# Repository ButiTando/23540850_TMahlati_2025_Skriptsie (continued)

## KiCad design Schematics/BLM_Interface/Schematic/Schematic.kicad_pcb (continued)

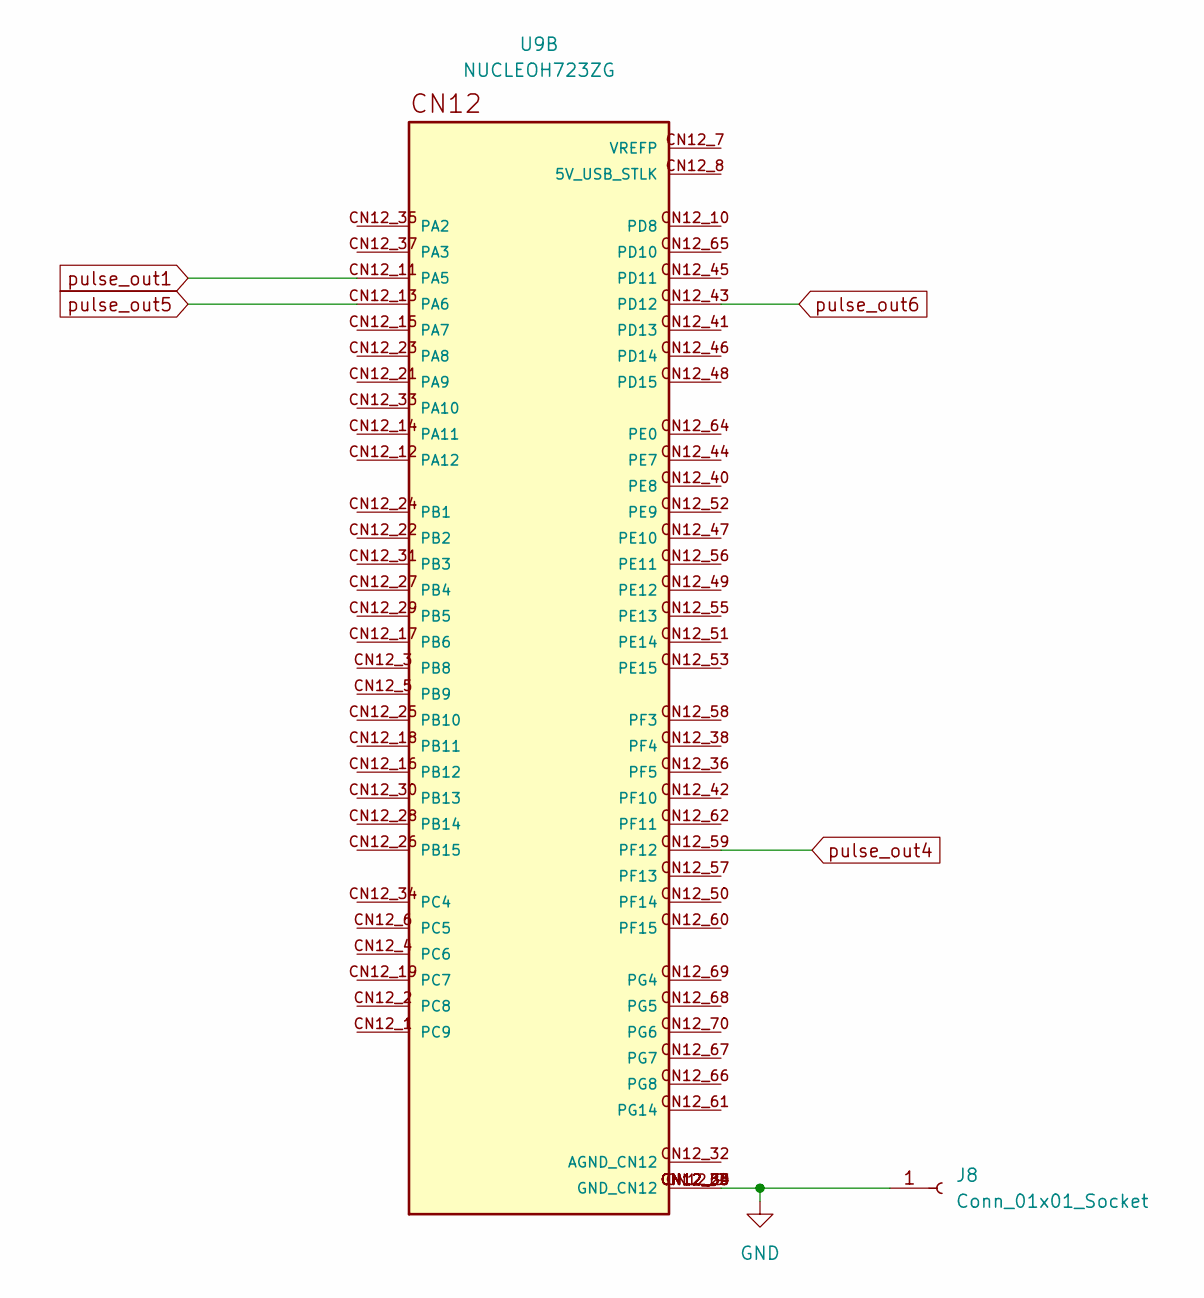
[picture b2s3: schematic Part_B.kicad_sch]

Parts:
J8: Conn_01x01_Socket; PinSocket_1x01_P2.54mm_Vertical
U9: NUCLEOH723ZG; MODULE_NUCLEOH723ZG; PARTREV 2

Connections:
GND: J8.1, U9.CN12_9 (GND_CN12), U9.CN12_20 (GND_CN12), U9.CN12_39 (GND_CN12), U9.CN12_54 (GND_CN12), U9.CN12_63 (GND_CN12); also elsewhere on the board
pulse_out1: U9.CN12_11 (PA5); also elsewhere on the board
pulse_out4: U9.CN12_59 (PF12); also elsewhere on the board
pulse_out5: U9.CN12_13 (PA6); also elsewhere on the board
pulse_out6: U9.CN12_43 (PD12); also elsewhere on the board

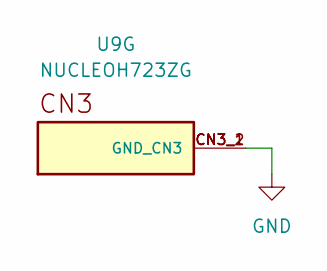
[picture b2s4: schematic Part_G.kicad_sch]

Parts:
U9: NUCLEOH723ZG; MODULE_NUCLEOH723ZG; PARTREV 2

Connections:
GND: U9.CN3_1 (GND_CN3), U9.CN3_2 (GND_CN3); also elsewhere on the board

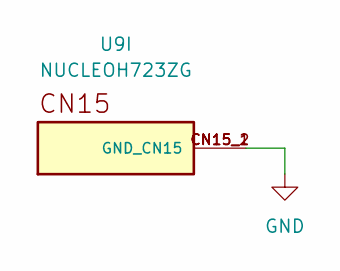
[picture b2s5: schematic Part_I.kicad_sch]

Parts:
U9: NUCLEOH723ZG; MODULE_NUCLEOH723ZG; PARTREV 2

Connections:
GND: U9.CN15_1 (GND_CN15), U9.CN15_2 (GND_CN15); also elsewhere on the board

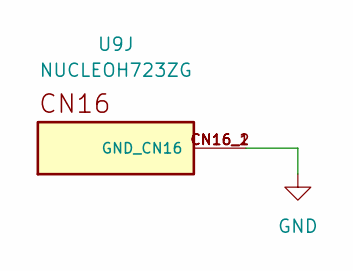
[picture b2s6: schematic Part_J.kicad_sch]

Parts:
U9: NUCLEOH723ZG; MODULE_NUCLEOH723ZG; PARTREV 2

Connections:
GND: U9.CN16_1 (GND_CN16), U9.CN16_2 (GND_CN16); also elsewhere on the board

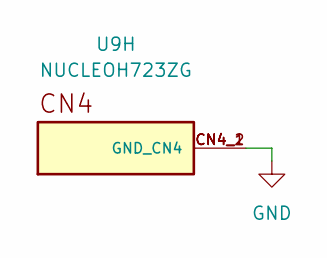
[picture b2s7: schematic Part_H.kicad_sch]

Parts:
U9: NUCLEOH723ZG; MODULE_NUCLEOH723ZG; PARTREV 2

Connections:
GND: U9.CN4_1 (GND_CN4), U9.CN4_2 (GND_CN4); also elsewhere on the board

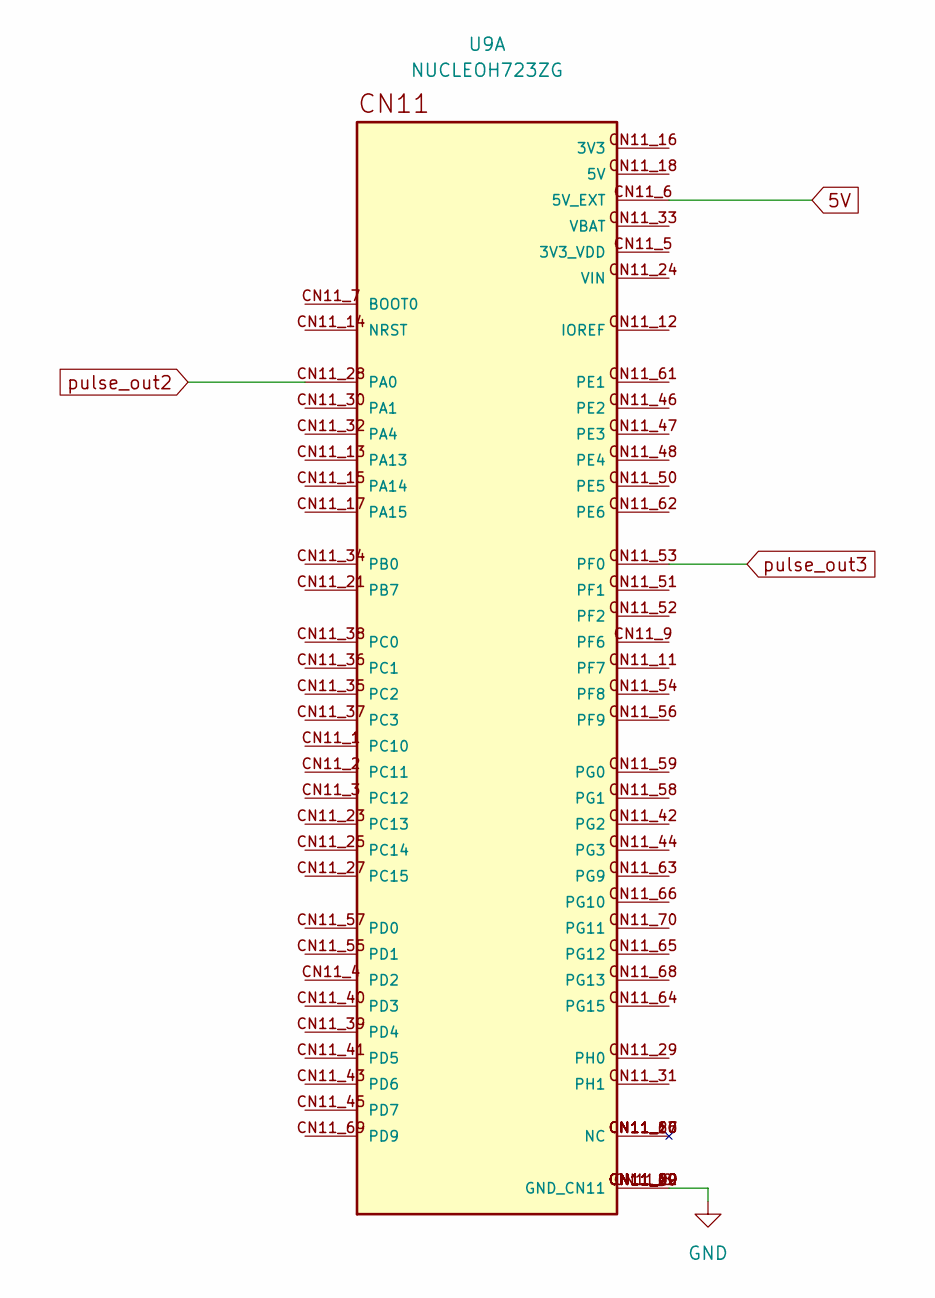
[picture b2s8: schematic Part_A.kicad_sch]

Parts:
U9: NUCLEOH723ZG; MODULE_NUCLEOH723ZG; PARTREV 2

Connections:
5V: U9.CN11_6 (5V_EXT); also elsewhere on the board
GND: U9.CN11_8 (GND_CN11), U9.CN11_19 (GND_CN11), U9.CN11_20 (GND_CN11), U9.CN11_22 (GND_CN11), U9.CN11_49 (GND_CN11), U9.CN11_60 (GND_CN11); also elsewhere on the board
pulse_out2: U9.CN11_28 (PA0); also elsewhere on the board
pulse_out3: U9.CN11_53 (PF0); also elsewhere on the board

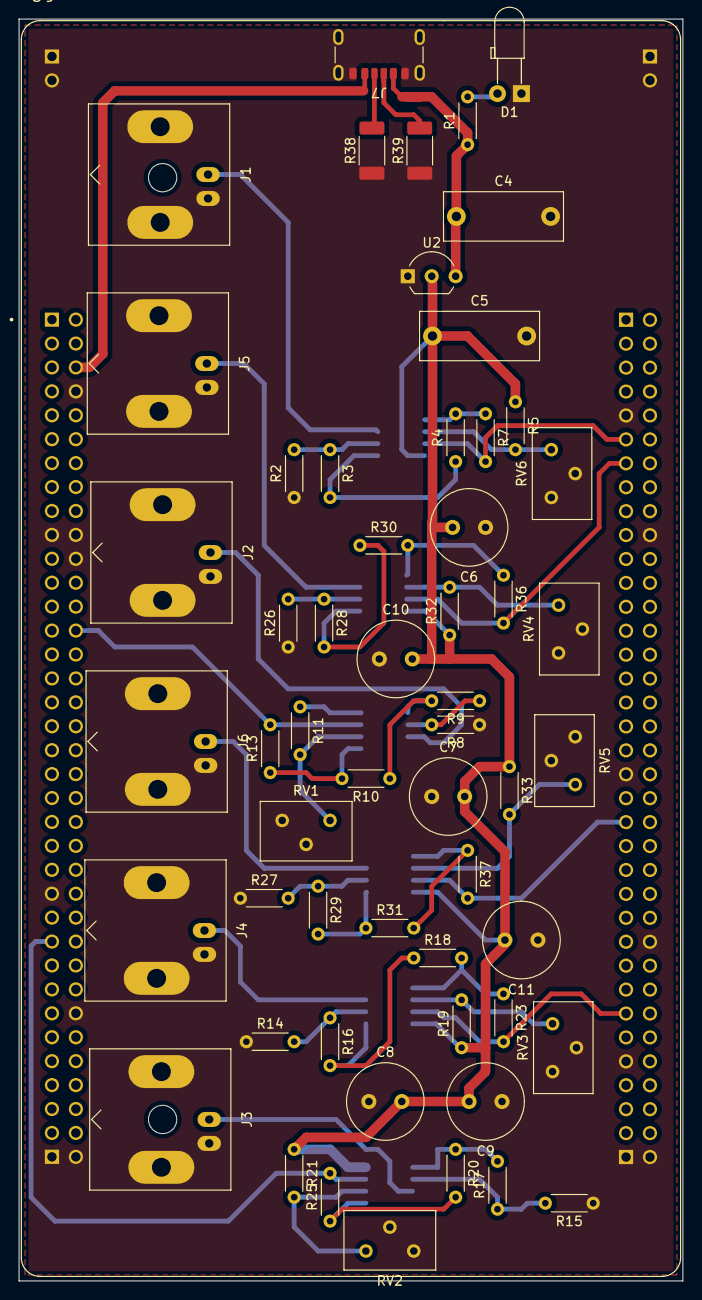
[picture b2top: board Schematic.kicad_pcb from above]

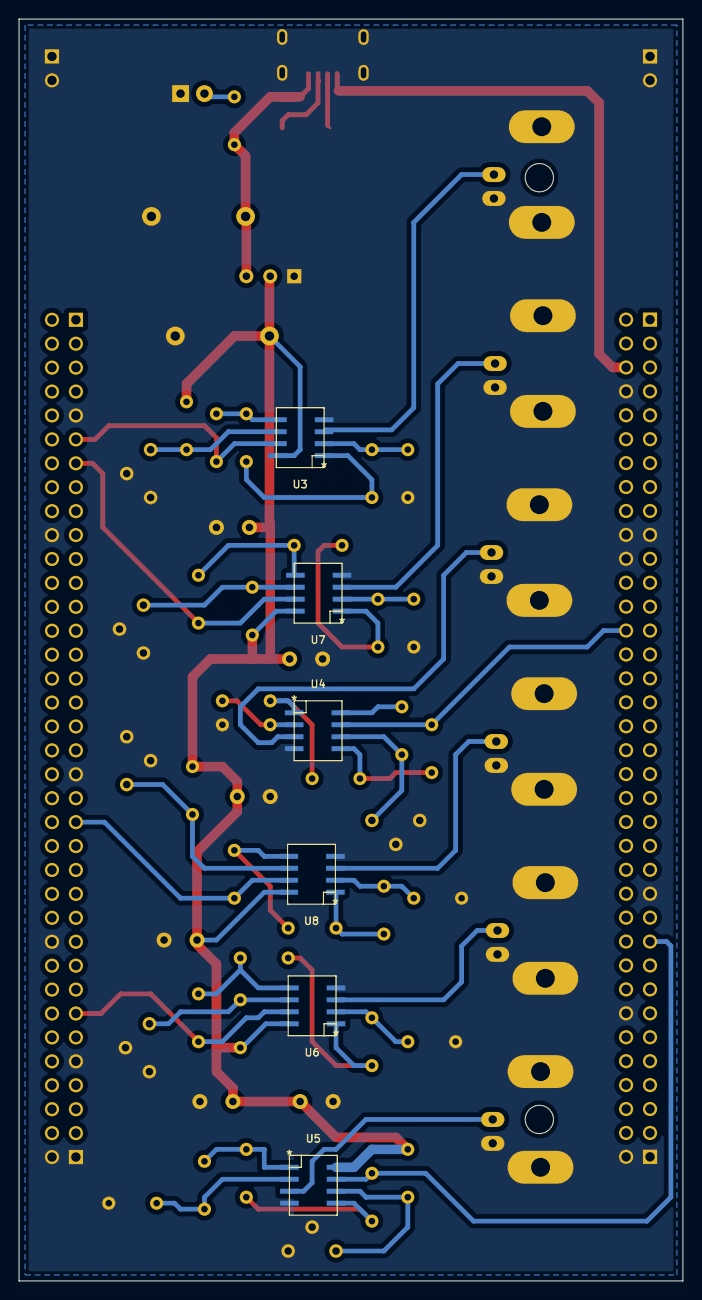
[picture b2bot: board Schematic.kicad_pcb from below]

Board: 2 copper layers, 70.5 x 134.0 mm, 63 parts (6 on the bottom side), 42 nets.

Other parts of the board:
C6, C7, C8, C9, C10, C11: 10u; C_Radial_D8.0mm_H11.5mm_P3.50mm

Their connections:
3V3: C6.2, C7.2, C8.2, C9.2, C10.2, C11.2; also elsewhere on the board
GND: C6.1, C7.1, C8.1, C9.1, C10.1, C11.1; also elsewhere on the board

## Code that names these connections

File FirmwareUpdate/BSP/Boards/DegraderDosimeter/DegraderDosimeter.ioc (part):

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Mcu.Name=STM32H723ZGTx
Mcu.Package=LQFP144
Mcu.UserName=STM32H723ZGTx
PA0.GPIOParameters=GPIO_Label
PA0.GPIO_Label=PULSE_2
PA0.Signal=S_TIM5_CH1
PA1.GPIOParameters=GPIO_Label
PA1.GPIO_Label=RMII_REF_CLK
PA1.Mode=RMII
PA1.Signal=ETH_REF_CLK
PA13(JTMS/SWDIO).GPIOParameters=GPIO_Label
PA13(JTMS/SWDIO).GPIO_Label=SWDIO
PA13(JTMS/SWDIO).Signal=DEBUG_JTMS-SWDIO
PA14(JTCK/SWCLK).GPIOParameters=GPIO_Label
PA14(JTCK/SWCLK).GPIO_Label=SWCLK
PA14(JTCK/SWCLK).Signal=DEBUG_JTCK-SWCLK
PA2.GPIOParameters=GPIO_Label
PA2.GPIO_Label=RMII_MDIO
PA2.Mode=RMII
PA2.Signal=ETH_MDIO
PA3.GPIOParameters=GPIO_PuPd,GPIO_Label
PA3.GPIO_Label=SW_3MM_LEFT
PA3.GPIO_PuPd=GPIO_PULLDOWN
PA3.Signal=GPIO_Input
PA5.GPIOParameters=GPIO_Label
PA5.GPIO_Label=PULSE_1
PA5.Signal=S_TIM2_CH1_ETR
PA6.GPIOParameters=GPIO_Label
PA6.GPIO_Label=PULSE_5
PA6.Signal=S_TIM3_CH1
PA7.GPIOParameters=GPIO_Label
PA7.GPIO_Label=RMII_CRS_DV
PA7.Mode=RMII
PA7.Signal=ETH_CRS_DV
PB13.GPIOParameters=GPIO_Label
PB13.GPIO_Label=RMII_TXD1
PB13.Mode=RMII
PB13.Signal=ETH_TXD1
PB14.GPIOParameters=GPIO_Label
PB14.GPIO_Label=STEP_PULSE
PB14.Signal=S_TIM12_CH1
PB2.GPIOParameters=GPIO_PuPd,PinState,GPIO_Label
PB2.GPIO_Label=STEP_NRESET
PB2.GPIO_PuPd=GPIO_PULLUP
PB2.PinState=GPIO_PIN_SET
PB2.Signal=GPIO_Output
PB3(JTDO/TRACESWO).GPIOParameters=GPIO_Label
PB3(JTDO/TRACESWO).GPIO_Label=SWO
PB3(JTDO/TRACESWO).Signal=DEBUG_JTDO-SWO
PB5.GPIOParameters=GPIO_PuPd,GPIO_Label
PB5.GPIO_Label=DC_MOTOR_EN
PB5.GPIO_PuPd=GPIO_PULLDOWN
PB5.Signal=GPIO_Output
PB6.GPIOParameters=GPIO_PuPd,PinState,GPIO_Label
PB6.GPIO_Label=STEP_NSLEEP
PB6.GPIO_PuPd=GPIO_PULLUP
PB6.PinState=GPIO_PIN_SET
PB6.Signal=GPIO_Output
PB7.GPIOParameters=GPIO_PuPd,PinState,GPIO_Label
PB7.GPIO_Label=STEP_NENABLE
PB7.GPIO_PuPd=GPIO_PULLUP
PB7.PinState=GPIO_PIN_SET
PB7.Signal=GPIO_Output
PC0.GPIOParameters=GPIO_PuPd,GPIO_Label
PC0.GPIO_Label=SW_12MM_SELECTED
PC0.GPIO_PuPd=GPIO_PULLDOWN
PC0.Signal=GPIO_Input
PC1.GPIOParameters=GPIO_Label
PC1.GPIO_Label=RMII_MDC
PC1.Mode=RMII
PC1.Signal=ETH_MDC
PC2_C.GPIOParameters=GPIO_PuPd,PinState,GPIO_Label
PC2_C.GPIO_Label=STEP_DIR
PC2_C.GPIO_PuPd=GPIO_NOPULL
PC2_C.PinState=GPIO_PIN_SET
PC2_C.Signal=GPIO_Output
PC3_C.GPIOParameters=GPIO_PuPd,GPIO_Label
PC3_C.GPIO_Label=SW_30MM_SELECTED
PC3_C.GPIO_PuPd=GPIO_PULLDOWN
PC3_C.Signal=GPIO_Input
PC4.GPIOParameters=GPIO_Label
PC4.GPIO_Label=RMII_RXD0
PC4.Mode=RMII
PC4.Signal=ETH_RXD0
PC5.GPIOParameters=GPIO_Label
PC5.GPIO_Label=RMII_RXD1
PC5.Mode=RMII
PC5.Signal=ETH_RXD1
PC6.GPIOParameters=GPIO_PuPd,GPIO_Label
PC6.GPIO_Label=DC_MOTOR_DIR2
PC6.GPIO_PuPd=GPIO_PULLDOWN
PC6.Signal=GPIO_Output
PC7.GPIOParameters=GPIO_PuPd,GPIO_Label
PC7.GPIO_Label=DC_MOTOR_DIR1
PC7.GPIO_PuPd=GPIO_PULLDOWN
PC7.Signal=GPIO_Output
PD0.GPIOParameters=GPIO_PuPd,GPIO_Label
PD0.GPIO_Label=SW_10MM_LEFT
PD0.GPIO_PuPd=GPIO_PULLDOWN
PD0.Signal=GPIO_Input
PD1.GPIOParameters=GPIO_PuPd,GPIO_Label
PD1.GPIO_Label=SW_2MM_LEFT
PD1.GPIO_PuPd=GPIO_PULLDOWN
PD1.Signal=GPIO_Input
PD12.GPIOParameters=GPIO_Label
PD12.GPIO_Label=PULSE_6
PD12.Signal=S_TIM4_CH1
PD13.GPIOParameters=GPIO_PuPd,GPIO_Label
PD13.GPIO_Label=STEP_MS3
PD13.GPIO_PuPd=GPIO_PULLDOWN
PD13.Signal=GPIO_Output
PD14.GPIOParameters=GPIO_PuPd,GPIO_Label
PD14.GPIO_Label=STEP_MS1
PD14.GPIO_PuPd=GPIO_PULLDOWN
PD14.Signal=GPIO_Output
PD15.GPIOParameters=GPIO_PuPd,GPIO_Label
PD15.GPIO_Label=STEP_MS2
PD15.GPIO_PuPd=GPIO_PULLDOWN
PD15.Signal=GPIO_Output
PD3.GPIOParameters=GPIO_PuPd,GPIO_Label
PD3.GPIO_Label=SW_2MM_SELECTED
PD3.GPIO_PuPd=GPIO_PULLDOWN
PD3.Signal=GPIO_Input
PD4.GPIOParameters=GPIO_PuPd,GPIO_Label
PD4.GPIO_Label=SW_10MM_RIGHT
PD4.GPIO_PuPd=GPIO_PULLDOWN
PD4.Signal=GPIO_Input
PD5.GPIOParameters=GPIO_PuPd,GPIO_Label
PD5.GPIO_Label=SW_30MM_RIGHT
PD5.GPIO_PuPd=GPIO_PULLDOWN
PD5.Signal=GPIO_Input
PD6.GPIOParameters=GPIO_PuPd,GPIO_Label
PD6.GPIO_Label=SW_12MM_RIGHT
PD6.GPIO_PuPd=GPIO_PULLDOWN
PD6.Signal=GPIO_Input
PD7.GPIOParameters=GPIO_PuPd,GPIO_Label
PD7.GPIO_Label=SW_6MM_LEFT
PD7.GPIO_PuPd=GPIO_PULLDOWN
PD7.Signal=GPIO_Input
PE2.GPIOParameters=GPIO_PuPd,GPIO_Label
PE2.GPIO_Label=SW_3MM_RIGHT
PE2.GPIO_PuPd=GPIO_PULLDOWN
PE2.Signal=GPIO_Input
PE3.GPIOParameters=GPIO_PuPd,GPIO_Label
PE3.GPIO_Label=SW_30MM_LEFT
PE3.GPIO_PuPd=GPIO_PULLDOWN
PE3.Signal=GPIO_Input
PE4.GPIOParameters=GPIO_PuPd,GPIO_Label
PE4.GPIO_Label=SW_6MM_RIGHT
PE4.GPIO_PuPd=GPIO_PULLDOWN
PE4.Signal=GPIO_Input
PE5.GPIOParameters=GPIO_PuPd,GPIO_Label
PE5.GPIO_Label=SW_2MM_RIGHT
PE5.GPIO_PuPd=GPIO_PULLDOWN
PE5.Signal=GPIO_Input
PE6.GPIOParameters=GPIO_PuPd,GPIO_Label
PE6.GPIO_Label=SW_8MM_RIGHT
PE6.GPIO_PuPd=GPIO_PULLDOWN
PE6.Signal=GPIO_Input
PF0.GPIOParameters=GPIO_Label
PF0.GPIO_Label=PULSE_3
PF0.Mode=TriggerSource_TI1FP1
PF0.Signal=TIM23_CH1
PF10.GPIOParameters=GPIO_PuPd,GPIO_Label
PF10.GPIO_Label=SW_12MM_LEFT
PF10.GPIO_PuPd=GPIO_PULLDOWN
PF10.Signal=GPIO_Input
PF12.GPIOParameters=GPIO_Label
PF12.GPIO_Label=PULSE_4
PF12.Mode=TriggerSource_TI2FP2
PF12.Signal=TIM24_CH2
PF2.GPIOParameters=GPIO_PuPd,GPIO_Label
PF2.GPIO_Label=SW_10MM_SELECTED
PF2.GPIO_PuPd=GPIO_PULLDOWN
PF2.Signal=GPIO_Input
PF3.GPIOParameters=GPIO_PuPd,GPIO_Label
PF3.GPIO_Label=SW_6MM_SELECTED
PF3.GPIO_PuPd=GPIO_PULLDOWN
PF3.Signal=GPIO_Input
PF5.GPIOParameters=GPIO_PuPd,GPIO_Label
PF5.GPIO_Label=SW_8MM_LEFT
PF5.GPIO_PuPd=GPIO_PULLDOWN
PF5.Signal=GPIO_Input
PF7.GPIOParameters=GPIO_PuPd,GPIO_Label
PF7.GPIO_Label=SW_8MM_SELECTED
PF7.GPIO_PuPd=GPIO_PULLDOWN
PF7.Signal=GPIO_Input
PF8.GPIOParameters=GPIO_PuPd,GPIO_Label
PF8.GPIO_Label=SW_3MM_SELECTED
PF8.GPIO_PuPd=GPIO_PULLDOWN
PF8.Signal=GPIO_Input
PG11.GPIOParameters=GPIO_Label
PG11.GPIO_Label=RMII_TX_EN
PG11.Mode=RMII
PG11.Signal=ETH_TX_EN
PG13.GPIOParameters=GPIO_Label
PG13.GPIO_Label=RMII_TXD0
PG13.Mode=RMII
PG13.Signal=ETH_TXD0
PH0-OSC_IN.Mode=HSE-External-Oscillator
PH0-OSC_IN.Signal=RCC_OSC_IN
PH1-OSC_OUT.Mode=HSE-External-Oscillator
PH1-OSC_OUT.Signal=RCC_OSC_OUT
RCC.HSE_VALUE=8000000
RCC.SYSCLKFreq_VALUE=550000000
RCC.SYSCLKSource=RCC_SYSCLKSOURCE_PLLCLK

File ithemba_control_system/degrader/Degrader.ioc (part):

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Mcu.Name=STM32F746ZGTx
Mcu.Package=LQFP144
Mcu.UserName=STM32F746ZGTx
PA1.Mode=RMII
PA1.Signal=ETH_REF_CLK
PA10.GPIOParameters=GPIO_Label
PA10.GPIO_Label=USB_ID
PA10.Signal=USB_OTG_FS_ID
PA11.GPIOParameters=GPIO_Label
PA11.GPIO_Label=USB_DM
PA11.Signal=USB_OTG_FS_DM
PA12.GPIOParameters=GPIO_Label
PA12.GPIO_Label=USB_DP
PA12.Signal=USB_OTG_FS_DP
PA13.GPIOParameters=GPIO_Label
PA13.GPIO_Label=TMS
PA13.Mode=Serial_Wire
PA13.Signal=SYS_JTMS-SWDIO
PA14.GPIOParameters=GPIO_Label
PA14.GPIO_Label=TCK
PA14.Mode=Serial_Wire
PA14.Signal=SYS_JTCK-SWCLK
PA2.GPIOParameters=GPIO_Label
PA2.GPIO_Label=RMII_MDIO [LAN8742A-CZ-TR_MDIO]
PA2.Mode=RMII
PA2.Signal=ETH_MDIO
PA3.GPIOParameters=GPIO_PuPd
PA3.GPIO_PuPd=GPIO_PULLDOWN
PA3.Signal=GPIO_Input
PA7.Mode=RMII
PA7.Signal=ETH_CRS_DV
PA8.GPIOParameters=GPIO_Label
PA8.GPIO_Label=USB_SOF [TP1]
PA8.Signal=USB_OTG_FS_SOF
PA9.GPIOParameters=GPIO_Label
PA9.GPIO_Label=USB_VBUS
PA9.Signal=USB_OTG_FS_VBUS
PB13.GPIOParameters=GPIO_Label
PB13.GPIO_Label=RMII_TXD1 [LAN8742A-CZ-TR_TXD1]
PB13.Mode=RMII
PB13.Signal=ETH_TXD1
PB14.Signal=S_TIM12_CH1
PB2.GPIOParameters=PinState,GPIO_PuPd
PB2.GPIO_PuPd=GPIO_PULLUP
PB2.PinState=GPIO_PIN_SET
PB2.Signal=GPIO_Output
PB3.GPIOParameters=GPIO_Label
PB3.GPIO_Label=SW0
PB3.Signal=SYS_JTDO-SWO
PB5.GPIOParameters=GPIO_PuPd
PB5.GPIO_PuPd=GPIO_PULLDOWN
PB5.Signal=GPIO_Output
PB6.GPIOParameters=PinState
PB6.PinState=GPIO_PIN_SET
PB6.Signal=GPIO_Output
PB8.Mode=I2C
PB8.Signal=I2C1_SCL
PB9.Mode=I2C
PB9.Signal=I2C1_SDA
PC0.GPIOParameters=GPIO_PuPd
PC0.GPIO_PuPd=GPIO_PULLDOWN
PC0.Signal=GPIO_Input
PC1.GPIOParameters=GPIO_Label
PC1.GPIO_Label=RMII_MDC [LAN8742A-CZ-TR_MDC]
PC1.Mode=RMII
PC1.Signal=ETH_MDC
PC13.GPIOParameters=GPIO_PuPd,GPIO_Label
PC13.GPIO_Label=USER_Btn [B1]
PC13.GPIO_PuPd=GPIO_PULLDOWN
PC13.Signal=GPXTI13
PC14/OSC32_IN.Mode=LSE-External-Oscillator
PC14/OSC32_IN.Signal=RCC_OSC32_IN
PC15/OSC32_OUT.Mode=LSE-External-Oscillator
PC15/OSC32_OUT.Signal=RCC_OSC32_OUT
PC2.GPIOParameters=PinState,GPIO_PuPd
PC2.GPIO_PuPd=GPIO_NOPULL
PC2.PinState=GPIO_PIN_SET
PC2.Signal=GPIO_Output
PC3.GPIOParameters=GPIO_PuPd
PC3.GPIO_PuPd=GPIO_PULLDOWN
PC3.Signal=GPIO_Input
PC4.GPIOParameters=GPIO_Label
PC4.GPIO_Label=RMII_RXD0 [LAN8742A-CZ-TR_RXD0]
PC4.Mode=RMII
PC4.Signal=ETH_RXD0
PC5.GPIOParameters=GPIO_Label
PC5.GPIO_Label=RMII_RXD1 [LAN8742A-CZ-TR_RXD1]
PC5.Mode=RMII
PC5.Signal=ETH_RXD1
PC6.GPIOParameters=GPIO_PuPd,GPIO_ModeDefaultOutputPP
PC6.GPIO_ModeDefaultOutputPP=GPIO_MODE_OUTPUT_PP
PC6.GPIO_PuPd=GPIO_PULLDOWN
PC6.Signal=GPIO_Output
PC7.GPIOParameters=GPIO_PuPd,GPIO_ModeDefaultOutputPP
PC7.GPIO_ModeDefaultOutputPP=GPIO_MODE_OUTPUT_PP
PC7.GPIO_PuPd=GPIO_PULLDOWN
PC7.Signal=GPIO_Output
PD0.GPIOParameters=GPIO_PuPd
PD0.GPIO_PuPd=GPIO_PULLDOWN
PD0.Signal=GPIO_Input
PD1.GPIOParameters=GPIO_PuPd
PD1.GPIO_PuPd=GPIO_PULLDOWN
PD1.Signal=GPIO_Input
PD11.GPIOParameters=GPIO_Speed,GPIO_PuPd
PD11.GPIO_PuPd=GPIO_PULLDOWN
PD11.GPIO_Speed=GPIO_SPEED_FREQ_LOW
PD11.Signal=GPIO_Output
PD12.GPIOParameters=PinState,GPIO_PuPd
PD12.GPIO_PuPd=GPIO_PULLDOWN
PD12.PinState=GPIO_PIN_RESET
PD12.Signal=GPIO_Output
PD13.GPIOParameters=GPIO_PuPd
PD13.GPIO_PuPd=GPIO_PULLDOWN
PD13.Signal=GPIO_Output
PD3.GPIOParameters=GPIO_PuPd
PD3.GPIO_PuPd=GPIO_PULLDOWN
PD3.Signal=GPIO_Input
PD4.GPIOParameters=GPIO_PuPd
PD4.GPIO_PuPd=GPIO_PULLDOWN
PD4.Signal=GPIO_Input
PD5.GPIOParameters=GPIO_PuPd
PD5.GPIO_PuPd=GPIO_PULLDOWN
PD5.Signal=GPIO_Input
PD6.GPIOParameters=GPIO_PuPd
PD6.GPIO_PuPd=GPIO_PULLDOWN
PD6.Signal=GPIO_Input
PD7.GPIOParameters=GPIO_PuPd
PD7.GPIO_PuPd=GPIO_PULLDOWN
PD7.Signal=GPIO_Input
PD8.GPIOParameters=GPIO_ModeDefaultPP,GPIO_Speed,GPIO_PuPd
PD8.GPIO_ModeDefaultPP=GPIO_MODE_AF_PP
PD8.GPIO_PuPd=GPIO_NOPULL
PD8.GPIO_Speed=GPIO_SPEED_FREQ_VERY_HIGH
PD8.Mode=Asynchronous
PD8.Signal=USART3_TX
PD9.GPIOParameters=GPIO_ModeDefaultPP,GPIO_Speed,GPIO_PuPd
PD9.GPIO_ModeDefaultPP=GPIO_MODE_AF_PP
PD9.GPIO_PuPd=GPIO_NOPULL
PD9.GPIO_Speed=GPIO_SPEED_FREQ_VERY_HIGH
PD9.Mode=Asynchronous
PD9.Signal=USART3_RX
PE2.GPIOParameters=GPIO_PuPd
PE2.GPIO_PuPd=GPIO_PULLDOWN
PE2.Signal=GPIO_Input
PE3.GPIOParameters=GPIO_PuPd
PE3.GPIO_PuPd=GPIO_PULLDOWN
PE3.Signal=GPIO_Input
PE4.GPIOParameters=GPIO_PuPd
PE4.GPIO_PuPd=GPIO_PULLDOWN
PE4.Signal=GPIO_Input
PE5.GPIOParameters=GPIO_PuPd
PE5.GPIO_PuPd=GPIO_PULLDOWN
PE5.Signal=GPIO_Input
PE6.GPIOParameters=GPIO_PuPd
PE6.GPIO_PuPd=GPIO_PULLDOWN
PE6.Signal=GPIO_Input
PF10.GPIOParameters=GPIO_PuPd
PF10.GPIO_PuPd=GPIO_PULLDOWN
PF10.Signal=GPIO_Input
PF2.GPIOParameters=GPIO_PuPd
PF2.GPIO_PuPd=GPIO_PULLDOWN
PF2.Signal=GPIO_Input
PF3.GPIOParameters=GPIO_PuPd
PF3.GPIO_PuPd=GPIO_PULLDOWN
PF3.Signal=GPIO_Input
PF5.GPIOParameters=GPIO_PuPd
PF5.GPIO_PuPd=GPIO_PULLDOWN
PF5.Signal=GPIO_Input
PF7.GPIOParameters=GPIO_PuPd
PF7.GPIO_PuPd=GPIO_PULLDOWN
PF7.Signal=GPIO_Input
PF8.GPIOParameters=GPIO_PuPd
PF8.GPIO_PuPd=GPIO_PULLDOWN
PF8.Signal=GPIO_Input
PG11.GPIOParameters=GPIO_Label
PG11.GPIO_Label=RMII_TX_EN [LAN8742A-CZ-TR_TXEN]
PG11.Mode=RMII
PG11.Signal=ETH_TX_EN
PG13.GPIOParameters=GPIO_Label
PG13.GPIO_Label=RMII_TXD0 [LAN8742A-CZ-TR_TXD0]
PG13.Mode=RMII
PG13.Signal=ETH_TXD0
PG6.GPIOParameters=GPIO_Label
PG6.GPIO_Label=USB_PowerSwitchOn [STMPS2151STR_EN]
PG6.Signal=GPIO_Output
PG7.GPIOParameters=GPIO_Label
PG7.GPIO_Label=USB_OverCurrent [STMPS2151STR_FAULT]
PG7.Signal=GPIO_Input
PH0/OSC_IN.GPIOParameters=GPIO_Label
PH0/OSC_IN.GPIO_Label=MCO [STM32F103CBT6_PA8]
PH0/OSC_IN.Mode=HSE-External-Clock-Source
PH0/OSC_IN.Signal=RCC_OSC_IN
PH1/OSC_OUT.Mode=HSE-External-Clock-Source
PH1/OSC_OUT.Signal=RCC_OSC_OUT
RCC.HSE_VALUE=8000000
RCC.SYSCLKFreq_VALUE=216000000
RCC.SYSCLKSource=RCC_SYSCLKSOURCE_PLLCLK
RCC.SYSCLKSourceVirtual=RCC_SYSCLKSOURCE_PLLCLK
board=NUCLEO-F746ZG
boardIOC=true
